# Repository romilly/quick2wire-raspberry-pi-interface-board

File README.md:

quick2wire-if-board
===================

This is the work-in-progress for the I/F Board.

-------------------------------------------------------
Copyright (c) 2013 Quick2Wire Ltd. http://quick2wire.com

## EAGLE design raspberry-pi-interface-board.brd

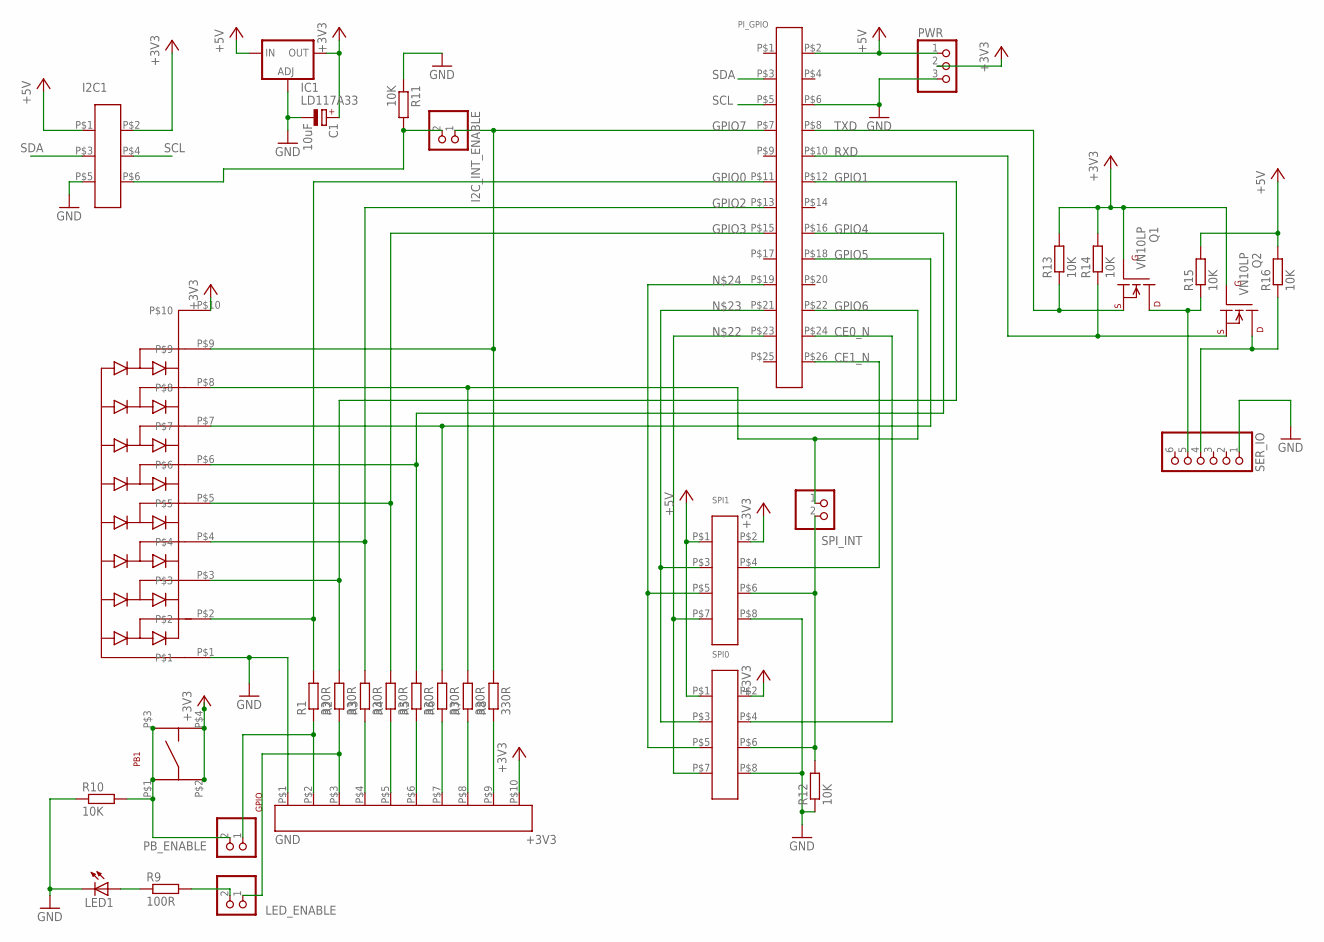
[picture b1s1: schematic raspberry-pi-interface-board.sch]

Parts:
C1: 10uF; E2,5-7
GPIO: APM-10W-SOCKET; AMP-10W-SOCKET
I2C1: IC2_0; IDC-6W
I2C_INT_ENABLE: PINHD-1X2; 1X02
IC1: LD117A33; TO220S
LED1: LED3MM
LED_ENABLE: PINHD-1X2; 1X02
PB1: TYCO-PUSHBUTTON
PB_ENABLE: PINHD-1X2; 1X02
PI_GPIO: IDC-26W
PWR: PINHD-1X3; 1X03
Q1, Q2: VN10LP; TO92
R1, R2, R3, R4, R5, R6, R7, R8: 330R; 0204/7
R9: 100R; 0207/10
R10, R11, R12, R13, R14, R15, R16: 10K; 0207/10
SER_IO: PINHD-1X6; 1X06
SPI0, SPI1: IDC-8W
SPI_INT: PINHD-1X2; 1X02
U$2: D10-5A

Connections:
+3V3: C1.+, GPIO.P$10, I2C1.P$2, IC1.2 (OUT), PB1.P$2, PB1.P$4, PWR.2, Q1.2 (G), Q2.2 (G), R13.2, R14.2, SPI0.P$2, SPI1.P$2, U$2.P$10
+5V: I2C1.P$1, IC1.3 (IN), PI_GPIO.P$2, PWR.1, R15.2, R16.2, SPI0.P$1, SPI1.P$1
CE0_N: PI_GPIO.P$24, SPI0.P$4
CE1_N: PI_GPIO.P$26, SPI1.P$4
GND: C1.-, GPIO.P$1, I2C1.P$5, IC1.1 (ADJ), LED1.K (C), PI_GPIO.P$6, PWR.3, R10.1, R11.1, R12.1, SER_IO.1, SPI0.P$8, SPI1.P$8, U$2.P$1
GPIO0: PI_GPIO.P$11, R1.2, U$2.P$2
GPIO1: PI_GPIO.P$12, R2.2, U$2.P$3
GPIO2: PI_GPIO.P$13, R3.2, U$2.P$4
GPIO3: PI_GPIO.P$15, R4.2, U$2.P$5
GPIO4: PI_GPIO.P$16, R5.2, U$2.P$6
GPIO5: PI_GPIO.P$18, R6.2, U$2.P$7
GPIO6: PI_GPIO.P$22, R7.2, SPI_INT.1, U$2.P$8
GPIO7: I2C_INT_ENABLE.1, PI_GPIO.P$7, R8.2, U$2.P$9
unnamed: PB1.P$1, PB1.P$3, PB_ENABLE.2, R10.2
unnamed: Q2.1 (D), R16.1, SER_IO.4
unnamed: GPIO.P$2, PB_ENABLE.1, R1.1
unnamed: GPIO.P$3, LED_ENABLE.1, R2.1
unnamed: GPIO.P$4, R3.1
unnamed: GPIO.P$5, R4.1
unnamed: GPIO.P$6, R5.1
unnamed: GPIO.P$7, R6.1
unnamed: GPIO.P$8, R7.1
unnamed: GPIO.P$9, R8.1
unnamed: Q1.1 (D), R15.1, SER_IO.5
unnamed: LED1.A, R9.1
unnamed: LED_ENABLE.2, R9.2
unnamed: I2C1.P$6, I2C_INT_ENABLE.2, R11.2
unnamed: PI_GPIO.P$23, SPI0.P$7, SPI1.P$7
unnamed: PI_GPIO.P$21, SPI0.P$3, SPI1.P$3
unnamed: PI_GPIO.P$19, SPI0.P$5, SPI1.P$5
unnamed: R12.2, SPI0.P$6, SPI1.P$6, SPI_INT.2
RXD: PI_GPIO.P$10, Q2.3 (S), R14.1
SCL: I2C1.P$4, PI_GPIO.P$5
SDA: I2C1.P$3, PI_GPIO.P$3
TXD: PI_GPIO.P$8, Q1.3 (S), R13.1

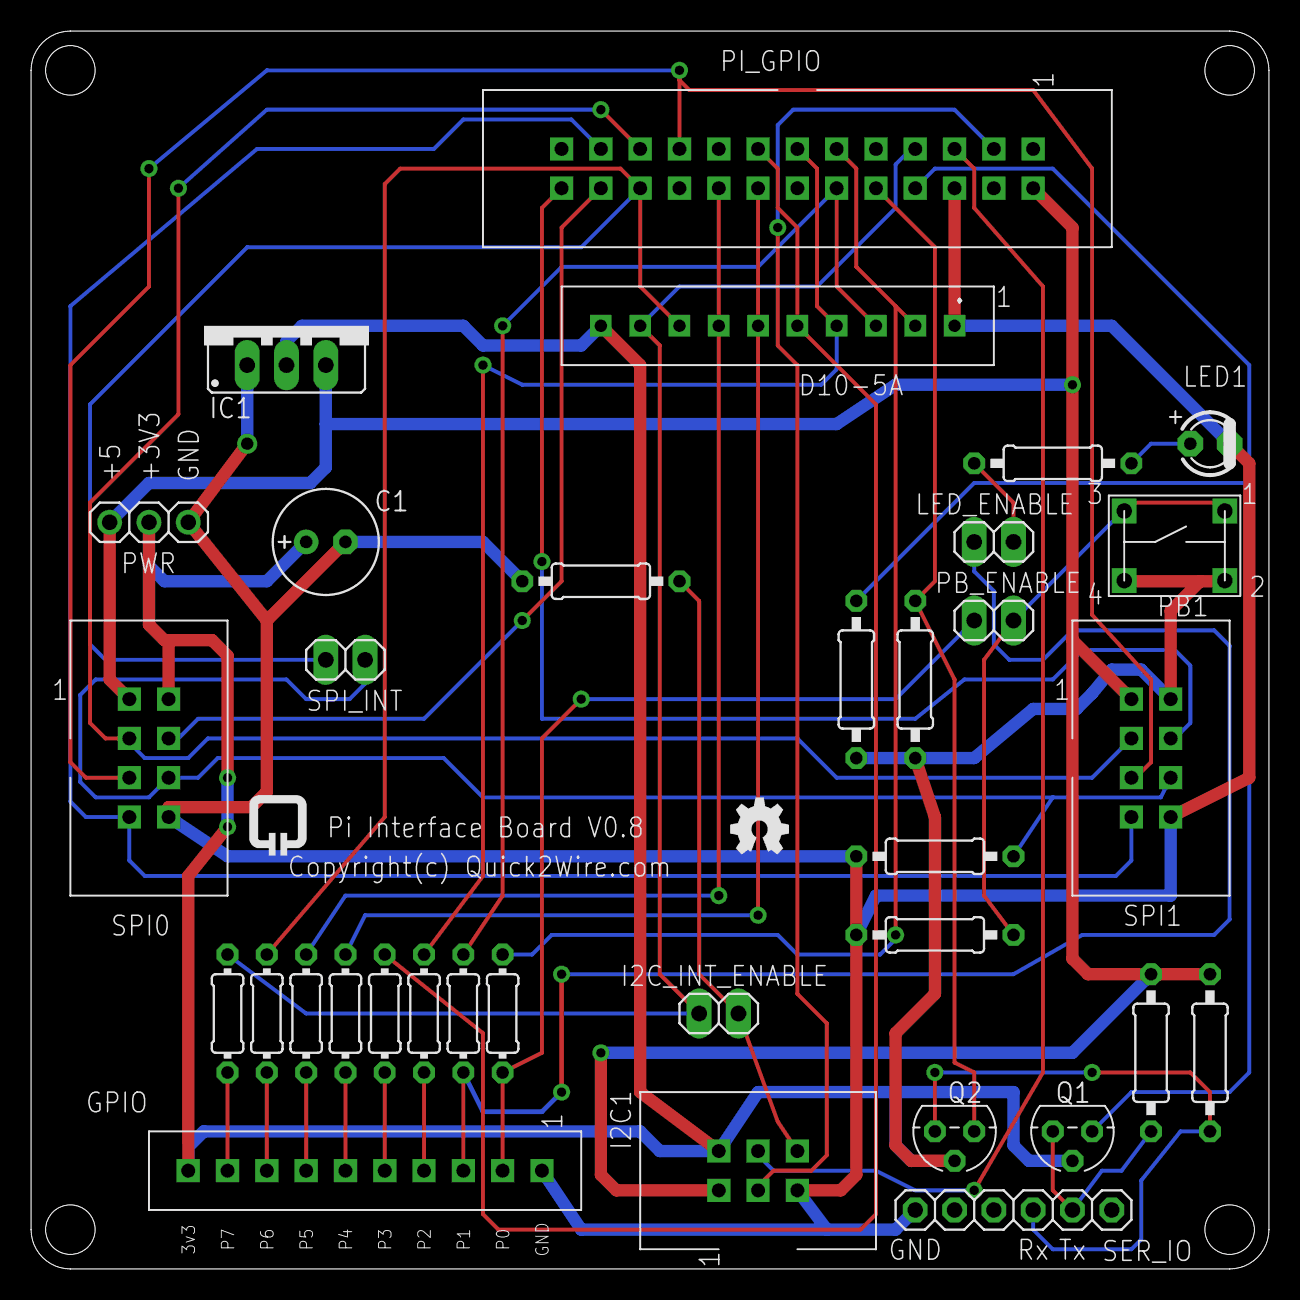
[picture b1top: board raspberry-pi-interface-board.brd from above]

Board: 2 copper layers, 80.0 x 80.0 mm, 37 parts (0 on the bottom side), 35 nets.

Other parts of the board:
U$1: OSHWLOGO_TOL_0.2
U$5: QUICK2WIRE-LOGO
U$6: OSHW-LOGO

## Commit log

2013-01-23 publishing version 0.7
2013-01-23 publishing version 0.8

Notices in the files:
raspberry-pi-interface-board.brd:
Copyright(c) Quick2Wire.com
